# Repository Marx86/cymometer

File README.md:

# cymometer
Сymometer on Attiny2313 and discrete counters

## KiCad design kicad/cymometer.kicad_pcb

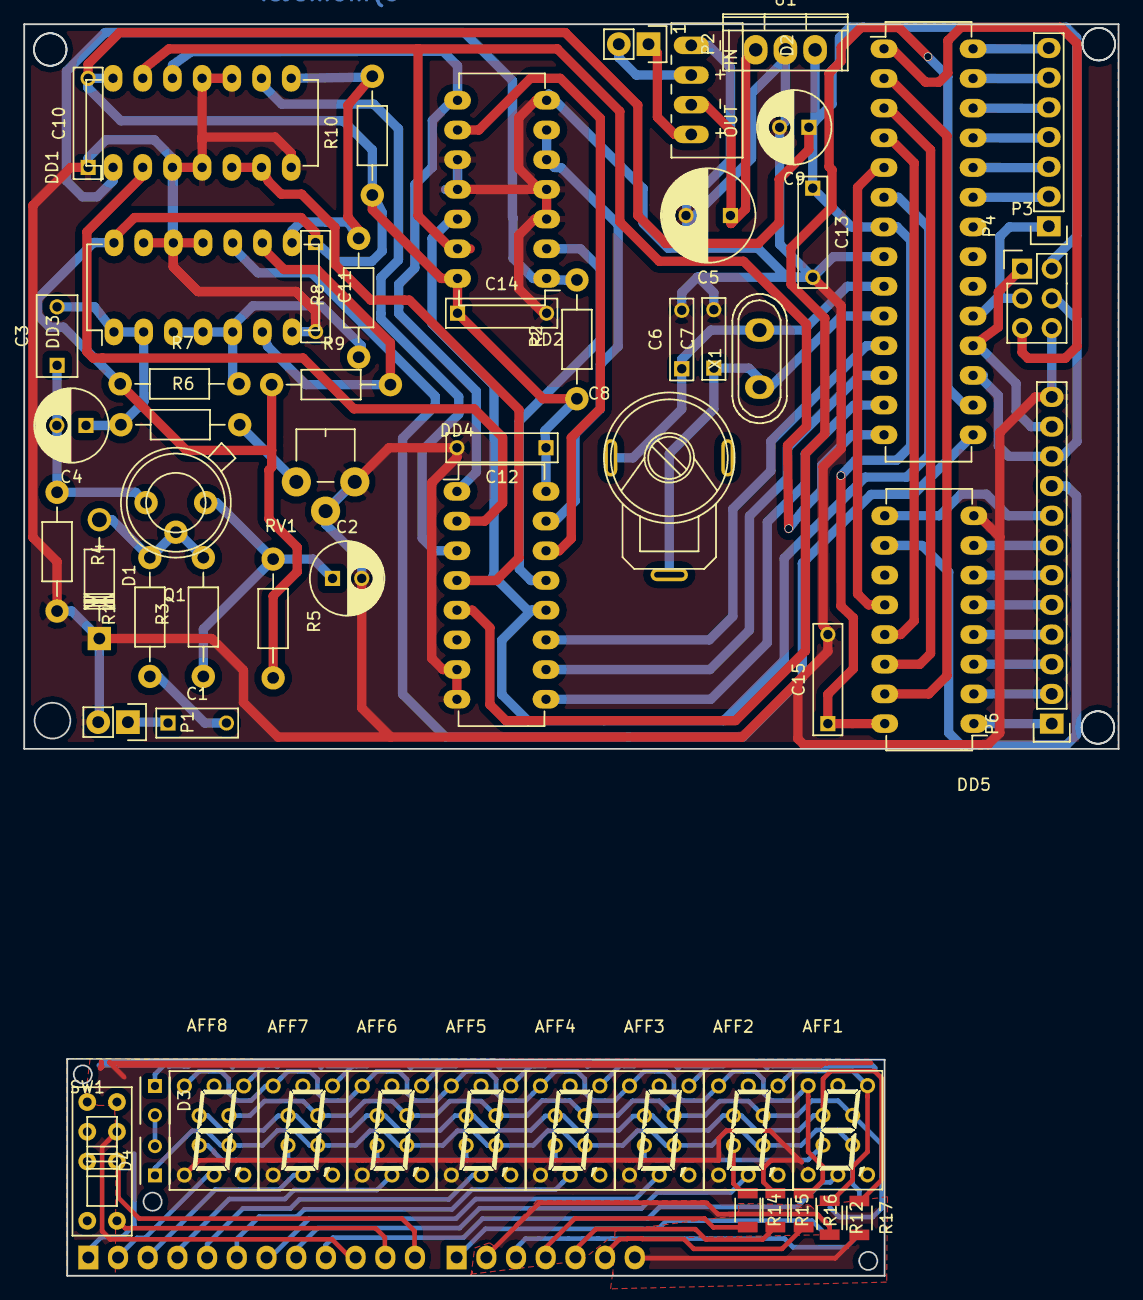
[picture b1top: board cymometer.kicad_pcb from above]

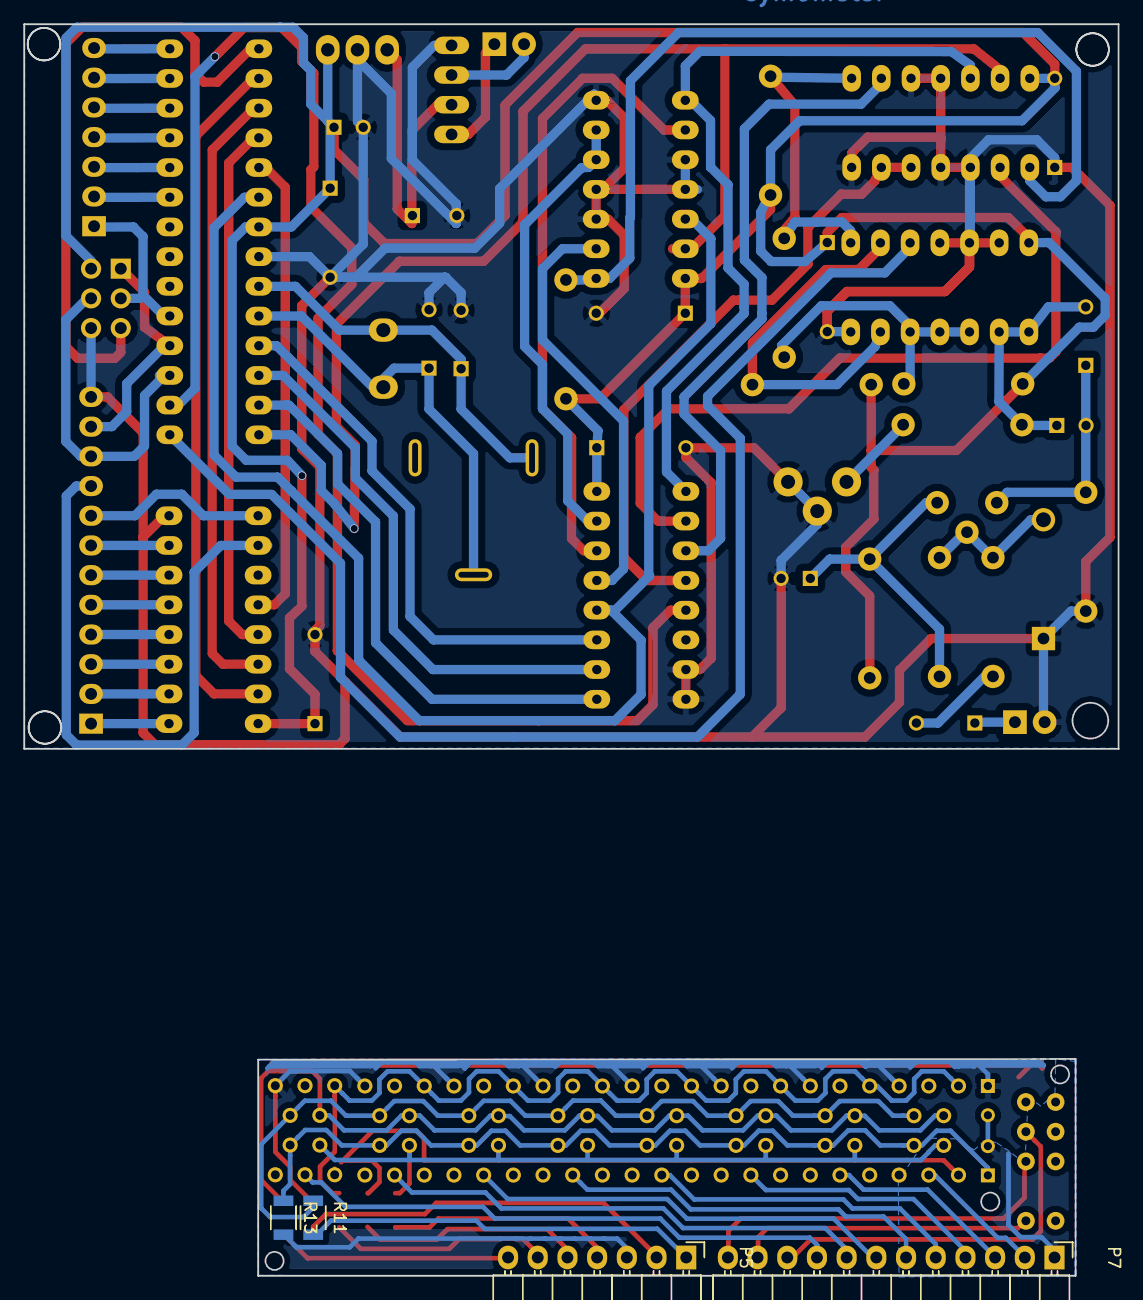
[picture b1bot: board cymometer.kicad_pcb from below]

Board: 2 copper layers, 93.6 x 107.0 mm, 62 parts (4 on the bottom side), 81 nets.

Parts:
AFF1, AFF2, AFF3, AFF4, AFF5, AFF6, AFF7, AFF8: 7SEGMENTS; 7segment_small1
C1: 0.22; C_Rect_L7_W2.5_P5
C2, C9: 100.0; C_Radial_D6.3_L11.2_P2.5
C3: 680; C_Rect_L7_W3.5_P5
C4: 22.0; C_Radial_D6.3_L11.2_P2.5
C5: 470.0; C_Radial_D8_L21_P3.8
C6, C7: C; C_Rect_L7_W2_P5
C8: CTRIM; кпк-мп
C10, C11, C12, C13, C14, C15: 0.1; C_Rect_L7_W2.5_P5
D1: КД503А; Diode_DO-41_SOD81_Horizontal_RM10
D2: BRIDGE; DCDC-Conv_TRACO_TME05xx_TME12xx
D3, D4: LED; C_Rect_L4_W2.5_P2.5
DD1, DD2: к531ие14; DIP-14_W7.62mm_LongPads
DD3: к155ла3; DIP-14_W7.62mm_LongPads
DD4: кр1533кп7; DIP-16_W7.62mm_LongPads
DD5: к155ид10; DIP-16_W7.62mm_LongPads
IC1: ATMEGA8-P; DIP-28_W7.62mm_LongPads
P1: BNC; Pin_Header_Straight_1x02
P2: CONN_2; Pin_Header_Straight_1x02
P3: CONN_3X2; Pin_Header_Straight_2x03
P4: CONN_7; Socket_Strip_Straight_1x07
P5: CONN_7; Pin_Header_Angled_1x07
P6: CONN_12; Socket_Strip_Straight_1x12
P7: CONN_12; Pin_Header_Angled_1x12
Q1: BC550; TO-43_3Pin
R1: 10k; Resistor_Horizontal_RM10mm
R2, R6: 1k; Resistor_Horizontal_RM10mm
R3: 150k; Resistor_Horizontal_RM10mm
R4: 360; Resistor_Horizontal_RM10mm
R5: 100; Resistor_Horizontal_RM10mm
R7, R9: 2.2k; Resistor_Horizontal_RM10mm
R8: 47k; Resistor_Horizontal_RM10mm
R10: 510; Resistor_Horizontal_RM10mm
R11, R12, R13, R14, R15, R16, R17: R; R_1206
RV1: 1k; Potentiometer_VishaySpectrol-Econtrim-Type36k
SW1: switch_3; switch3
U1: 7805; TO-220
X1: 20.48 MГц; Crystal_HC50-U_Vertical

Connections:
GND: C2.2, C5.2, C6.2, C7.2, C9.2, C10.1, C11.2, C12.2, C13.2, C14.2, C15.2, D1.1, D2.1, DD1.3, DD1.4, DD1.7, DD1.10, DD1.11, DD2.3, DD2.4, DD2.7, DD2.10, DD2.11, DD3.7, DD3.11, DD3.12, DD3.13, DD4.7, DD4.8, DD5.8, IC1.8, P1.2, P3.6, P6.12, R4.2, RV1.1, RV1.2, U1.2
unnamed: AFF1.1, AFF2.1, AFF3.1, AFF4.1, AFF5.1, AFF6.1, AFF7.1, AFF8.1, R15.1
unnamed: AFF1.2, AFF2.2, AFF3.2, AFF4.2, AFF5.2, AFF6.2, AFF7.2, AFF8.2, R14.1
unnamed: AFF1.3, P7.9
unnamed: AFF1.4, AFF2.4, AFF3.4, AFF4.4, AFF5.4, AFF6.4, AFF7.4, AFF8.4, D4.1, R13.1
unnamed: AFF1.6, AFF2.6, AFF3.6, AFF4.6, AFF5.6, AFF6.6, AFF7.6, AFF8.6, D3.1, R12.1
unnamed: AFF1.7, AFF2.7, AFF3.7, AFF4.7, AFF5.7, AFF6.7, AFF7.7, AFF8.7, R11.1
unnamed: AFF1.9, AFF2.9, AFF3.9, AFF4.9, AFF5.9, AFF6.9, AFF7.9, AFF8.9, R16.1
unnamed: AFF1.10, AFF2.10, AFF3.10, AFF4.10, AFF5.10, AFF6.10, AFF7.10, AFF8.10, R17.1
unnamed: AFF2.3, P7.8
unnamed: AFF3.3, P7.7
unnamed: AFF4.3, P7.6
unnamed: AFF5.3, P7.5
unnamed: AFF6.3, P7.4
unnamed: AFF7.3, P7.3
unnamed: AFF8.3, P7.2
unnamed: C1.1, P1.1
unnamed: C1.2, R1.1
unnamed: C2.1, Q1.1, R3.1, R5.1
unnamed: C3.1, C4.2, Q1.3, R4.1
unnamed: C3.2, C4.1, DD3.1, DD3.2, R6.1
unnamed: C5.1, D2.3, U1.1
unnamed: C6.1, C8.1, IC1.9, X1.2
unnamed: C7.1, C8.2, IC1.10, X1.1
unnamed: D1.2, Q1.2, R1.2, R3.2
unnamed: D2.2, P2.2
unnamed: D2.4, P2.1
unnamed: D3.2, D4.2, P7.1
unnamed: DD1.1, DD2.1, R2.2
unnamed: DD1.2, DD4.2
unnamed: DD1.5, DD1.6, DD4.4
unnamed: DD1.8, DD3.8, R8.2, R10.2
unnamed: DD1.9, DD4.3
unnamed: DD1.12, DD2.8, DD4.1
unnamed: DD1.13, DD2.13, IC1.14
unnamed: DD2.2, DD4.13
unnamed: DD2.5, DD2.6, DD4.15
unnamed: DD2.9, DD4.14
unnamed: DD2.12, DD4.12, IC1.6
unnamed: DD3.3, DD3.4, DD3.5, R7.2, R8.1
unnamed: DD3.6, DD3.9, R9.2
unnamed: DD3.10, IC1.15
unnamed: DD4.5, IC1.16
unnamed: DD4.9, IC1.13
unnamed: DD4.10, IC1.12
unnamed: DD4.11, IC1.11
unnamed: DD5.1, P6.1
unnamed: DD5.2, P6.2
unnamed: DD5.3, P6.3
unnamed: DD5.4, P6.4
unnamed: DD5.5, P6.5
unnamed: DD5.6, P6.6
unnamed: DD5.7, P6.7
unnamed: DD5.9, P6.8
unnamed: DD5.10, P6.9
unnamed: DD5.12, IC1.5
unnamed: DD5.13, IC1.4
unnamed: DD5.14, IC1.3
unnamed: DD5.15, IC1.2
unnamed: IC1.1, P3.5
unnamed: IC1.17, P3.4, P6.10
unnamed: IC1.18, P3.1, P6.11
unnamed: IC1.19, P3.3, P4.1
unnamed: IC1.23, P4.2
unnamed: IC1.24, P4.3
unnamed: IC1.25, P4.4
unnamed: IC1.26, P4.5
unnamed: IC1.27, P4.6
unnamed: IC1.28, P4.7
unnamed: P5.1, R11.2
unnamed: P5.2, R12.2
unnamed: P5.3, R13.2
unnamed: P5.4, R14.2
unnamed: P5.5, R15.2
unnamed: P5.6, R16.2
unnamed: P5.7, R17.2
unnamed: P7.10, SW1.3
unnamed: P7.11, SW1.2
unnamed: P7.12, SW1.1
unnamed: R6.2, RV1.3
VCC: C9.1, C10.2, C11.1, C12.1, C13.1, C14.1, C15.1, DD1.14, DD2.14, DD3.14, DD4.16, DD5.16, IC1.7, P3.2, R2.1, R5.2, R7.1, R9.1, R10.1, U1.3

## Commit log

2016-03-09 Add kicad files
2016-03-10 Update circuit
2016-03-11 Add src
2016-03-16 Add new circuit
2016-03-21 Add libraries
2016-03-22 Add display
2016-03-23 Add display board
2016-04-01 Modified circuit for Atmega8-p
2016-04-21 Add all
2016-05-10 End board
2016-05-13 New commit
2016-05-17 End the tracing
2016-06-06 change switch
2016-07-04 Add mask to board
2018-01-23 Add size
